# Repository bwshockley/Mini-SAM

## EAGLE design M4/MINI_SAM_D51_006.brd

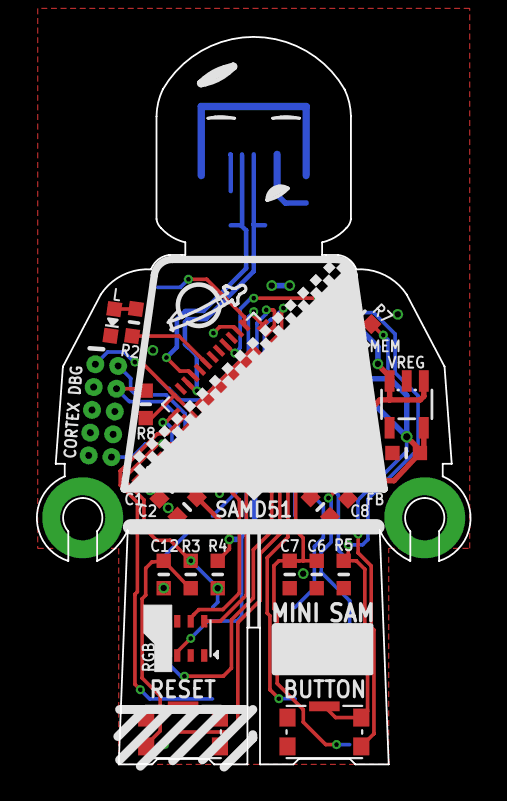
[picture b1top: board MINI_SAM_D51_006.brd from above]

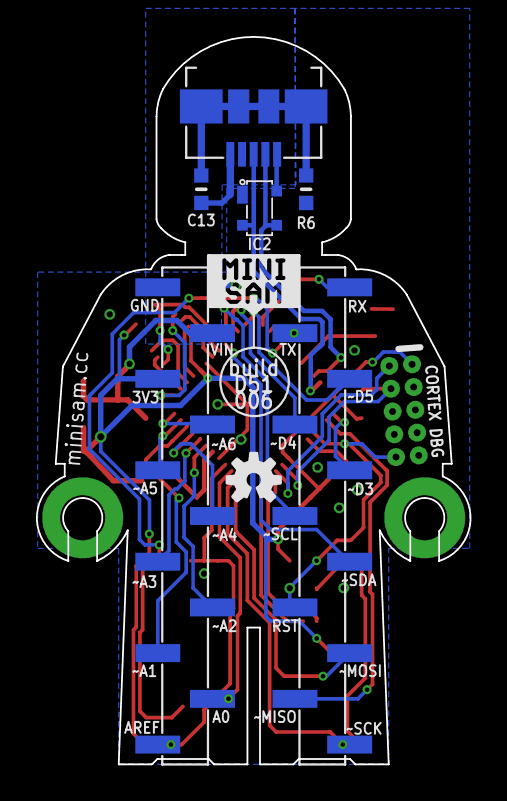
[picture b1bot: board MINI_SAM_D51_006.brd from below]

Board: 2 copper layers, 24.1 x 40.4 mm, 32 parts (7 on the bottom side), 41 nets.

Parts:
C1, C3, C7, C8, C12: 0.1µF; _0603MP
C2, C9, C10, C11: 10µF; _0603MP
C6: 4.7µF; _0603MP
C13: 4.7nF; _0603MP
FB: _0603MP
IC2: PRTR5V0U2X; SOT143B_REFLOW
IC4: ATSAMD51G_TQFN48; TQFN48_7MM
J1: MOLEX_47346-100147346; MOLEX_47346-1001
J2: CORTEX_DEBUG_PTH; 2X5-PTH-1.27MM
J3, J4: 1X11_SMT
L: CHIPLED_0603_NOOUTLINE
R2, R8: 1k; _0603MP
R3: 330Ohm; _0603MP
R4, R5: 10K; _0603MP
R6: 1M; _0603MP
R7: 100k; _0603MP
RGB: AP102-2020; APA102_2020
SW1, SW2: KMS233GLFG; KMS_SWITCH
U1: GD25x16; USON8
U$3: OSHW-LOGO-S
VREG: AP2112K-3.3V; SOT23-5

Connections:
!RESET: IC4.40, J2.10, J4.8, R3.1, R4.1
A0: IC4.3, J3.2
A1: IC4.10, J3.3
A2: IC4.7, J3.4
A3: IC4.8, J3.5
A4: IC4.9, J3.6
A5: IC4.11, J3.7
A6_D2: IC4.12, J3.8
AREF: C6.1, C7.1, IC4.4, J3.1
D3: IC4.37, J4.5
D4: IC4.23, J4.4
D5: IC4.24, J4.3
D9: IC4.28, R5.2, SW2.3, SW2.4
D13: IC4.31, R2.2
DOTSTAR_CLK: IC4.47, RGB.5
DOTSTAR_DATA: IC4.48, RGB.6
GND: C1.2, C2.2, C3.2, C6.2, C7.2, C8.2, C9.2, C10.1, C11.2, C12.1, C13.2, IC2.P1, IC4.5, IC4.18, IC4.35, IC4.42, IC4.THERMAL, J1.P5, J2.3, J2.5, J3.11, L.C, R5.1, R6.1, RGB.4, SW1.3, SW1.4, U1.4, VREG.2
MISO: IC4.38, J4.10
MOSI: IC4.1, J4.9
unnamed: C13.1, J1.PAD1, J1.PAD2, J1.PAD3, J1.PAD4, R6.2
unnamed: L.A, R2.1
unnamed: C12.2, R3.2, SW1.1
unnamed: C1.1, IC4.41
QSPI_CS: IC4.20, R7.2, U1.1
QSPI_DATA[0]: IC4.13, U1.5
QSPI_DATA[1]: IC4.14, U1.2
QSPI_DATA[2]: IC4.15, U1.3
QSPI_DATA[3]: IC4.16, U1.7
QSPI_SCK: IC4.19, U1.6
RX_D0: IC4.25, J4.1
SCK: IC4.2, J4.11
SCL: IC4.22, J4.6
SDA: IC4.21, J4.7
SWCLK: IC4.45, J2.4, R8.1
SWDIO: IC4.46, J2.2
TX_D1: IC4.26, J4.2
USBD+: IC2.P2, IC4.34, J1.P3
USBD-: IC2.P$3, IC4.33, J1.P2
VDD: C2.1, C3.1, C11.1, FB.1, IC4.17, IC4.36, IC4.44, J2.1, J3.9, R4.2, R7.1, R8.2, RGB.3, SW2.5, U1.8, VREG.5
VDDANA: C8.1, C9.1, FB.2, IC4.6
VIN: C10.2, IC2.P$4, J1.P1, J3.10, VREG.1, VREG.3

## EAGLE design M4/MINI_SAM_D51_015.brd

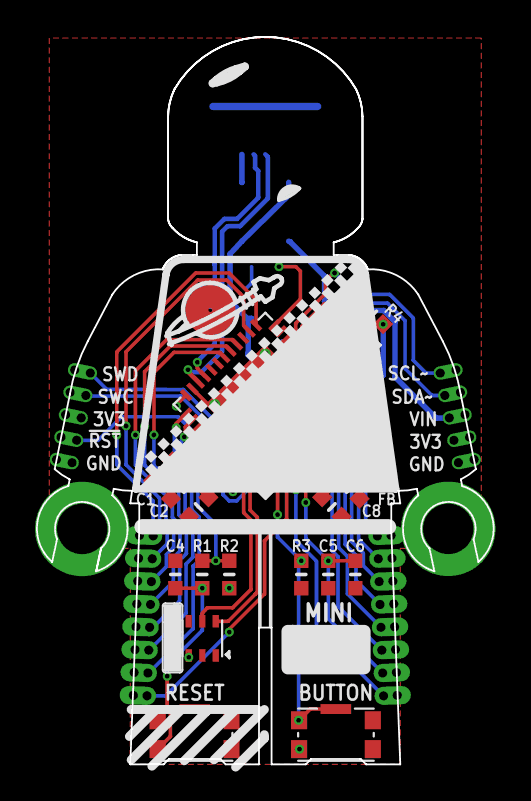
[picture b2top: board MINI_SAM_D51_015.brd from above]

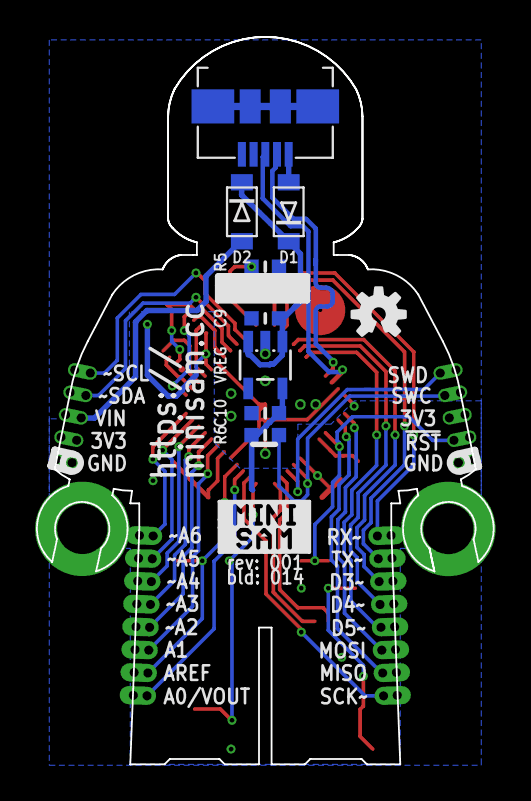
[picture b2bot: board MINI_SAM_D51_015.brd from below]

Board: 2 copper layers, 25.4 x 40.4 mm, 32 parts (10 on the bottom side), 42 nets.

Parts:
C1, C3, C4, C6, C8: 0.1µF; _0603MP
C2, C7, C9, C10: 10µF; _0603MP
C5: 4.7µF; _0603MP
D1, D2: MBR120; SOD-123FL
FB: _0603MP
J1: MOLEX_47346-100147346; MOLEX_47346-1001
J2, J4: 1X5_HEADER_1.27MMCAST; 1X5_HEADER_1.27MM_CASTELLATED
J3, J5: 1X8_HEADER_1.27MMCAST; 1X8_HEADER_1.27MM_CASTELLATED
LED: CHIPLED_0805_NOOUTLINE
R1: 1K; _0603MP
R2, R3: 10K; _0603MP
R4: 100k; _0603MP
R5, R6: 1k; _0603MP
RGB: AP102-2020; APA102_2020
SW1, SW2: KMS233GLFG; KMS_SWITCH
U1: ATSAMD51G_TQFN48; TQFN48_7MM
U2: GD25x16; USON8
U$3: OSHW-LOGO-S
VREG: AP2112K-3.3V; SOT23-5

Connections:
!RESET: J2.P4, R1.1, R2.1, U1.40
A0: J5.P1, U1.3
A1: J5.P3, U1.7
A2: J5.P4, U1.8
A3: J5.P5, U1.9
A4: J5.P6, U1.10
A5: J5.P7, U1.11
A6: J5.P8, U1.12
AREF: C5.1, C6.1, J5.P2, U1.4
BUTTON_D6: R3.2, SW2.2, SW2.3, U1.1
D3: J3.P3, U1.28
D4: J3.P4, U1.29
D5: J3.P5, U1.30
D14: R5.2, U1.24
DOTSTAR_CLK: RGB.5, U1.47
DOTSTAR_DATA: RGB.6, U1.48
GND: C1.2, C2.2, C3.2, C4.1, C5.2, C6.2, C7.2, C8.2, C9.1, C10.2, J1.P5, J1.PAD1, J1.PAD2, J1.PAD3, J1.PAD4, J2.P5, J4.P1, LED.C, R3.1, RGB.4, SW1.3, SW1.4, U1.5, U1.18, U1.35, U1.42, U1.THERMAL, U2.4, VREG.2
MISO: J3.P7, U1.38
MOSI: J3.P6, U1.37
unnamed: LED.A, R5.1
unnamed: C4.2, R1.2, SW1.1
unnamed: C1.1, U1.41
QSPI_CS: R4.2, U1.20, U2.1
QSPI_DATA[0]: U1.13, U2.5
QSPI_DATA[1]: U1.14, U2.2
QSPI_DATA[2]: U1.15, U2.3
QSPI_DATA[3]: U1.16, U2.7
QSPI_SCK: U1.19, U2.6
RX_D0: J3.P1, U1.25
SCK: J3.P8, U1.2
SCL: J4.P5, U1.22
SDA: J4.P4, U1.21
SWCLK: J2.P2, R6.1, U1.45
SWDIO: J2.P1, U1.46
TX_D1: J3.P2, U1.26
USBD+: J1.P3, U1.34
USBD-: J1.P2, U1.33
VDD: C2.1, C3.1, C10.1, FB.1, J2.P3, J4.P2, R2.2, R4.1, R6.2, RGB.3, SW2.1, U1.17, U1.36, U1.44, U2.8, VREG.5
VDDANA: C7.1, C8.1, FB.2, U1.6
VHI: C9.2, D1.C, D2.C, VREG.1, VREG.3
VIN: D2.A, J4.P3
VUSB: D1.A, J1.P1

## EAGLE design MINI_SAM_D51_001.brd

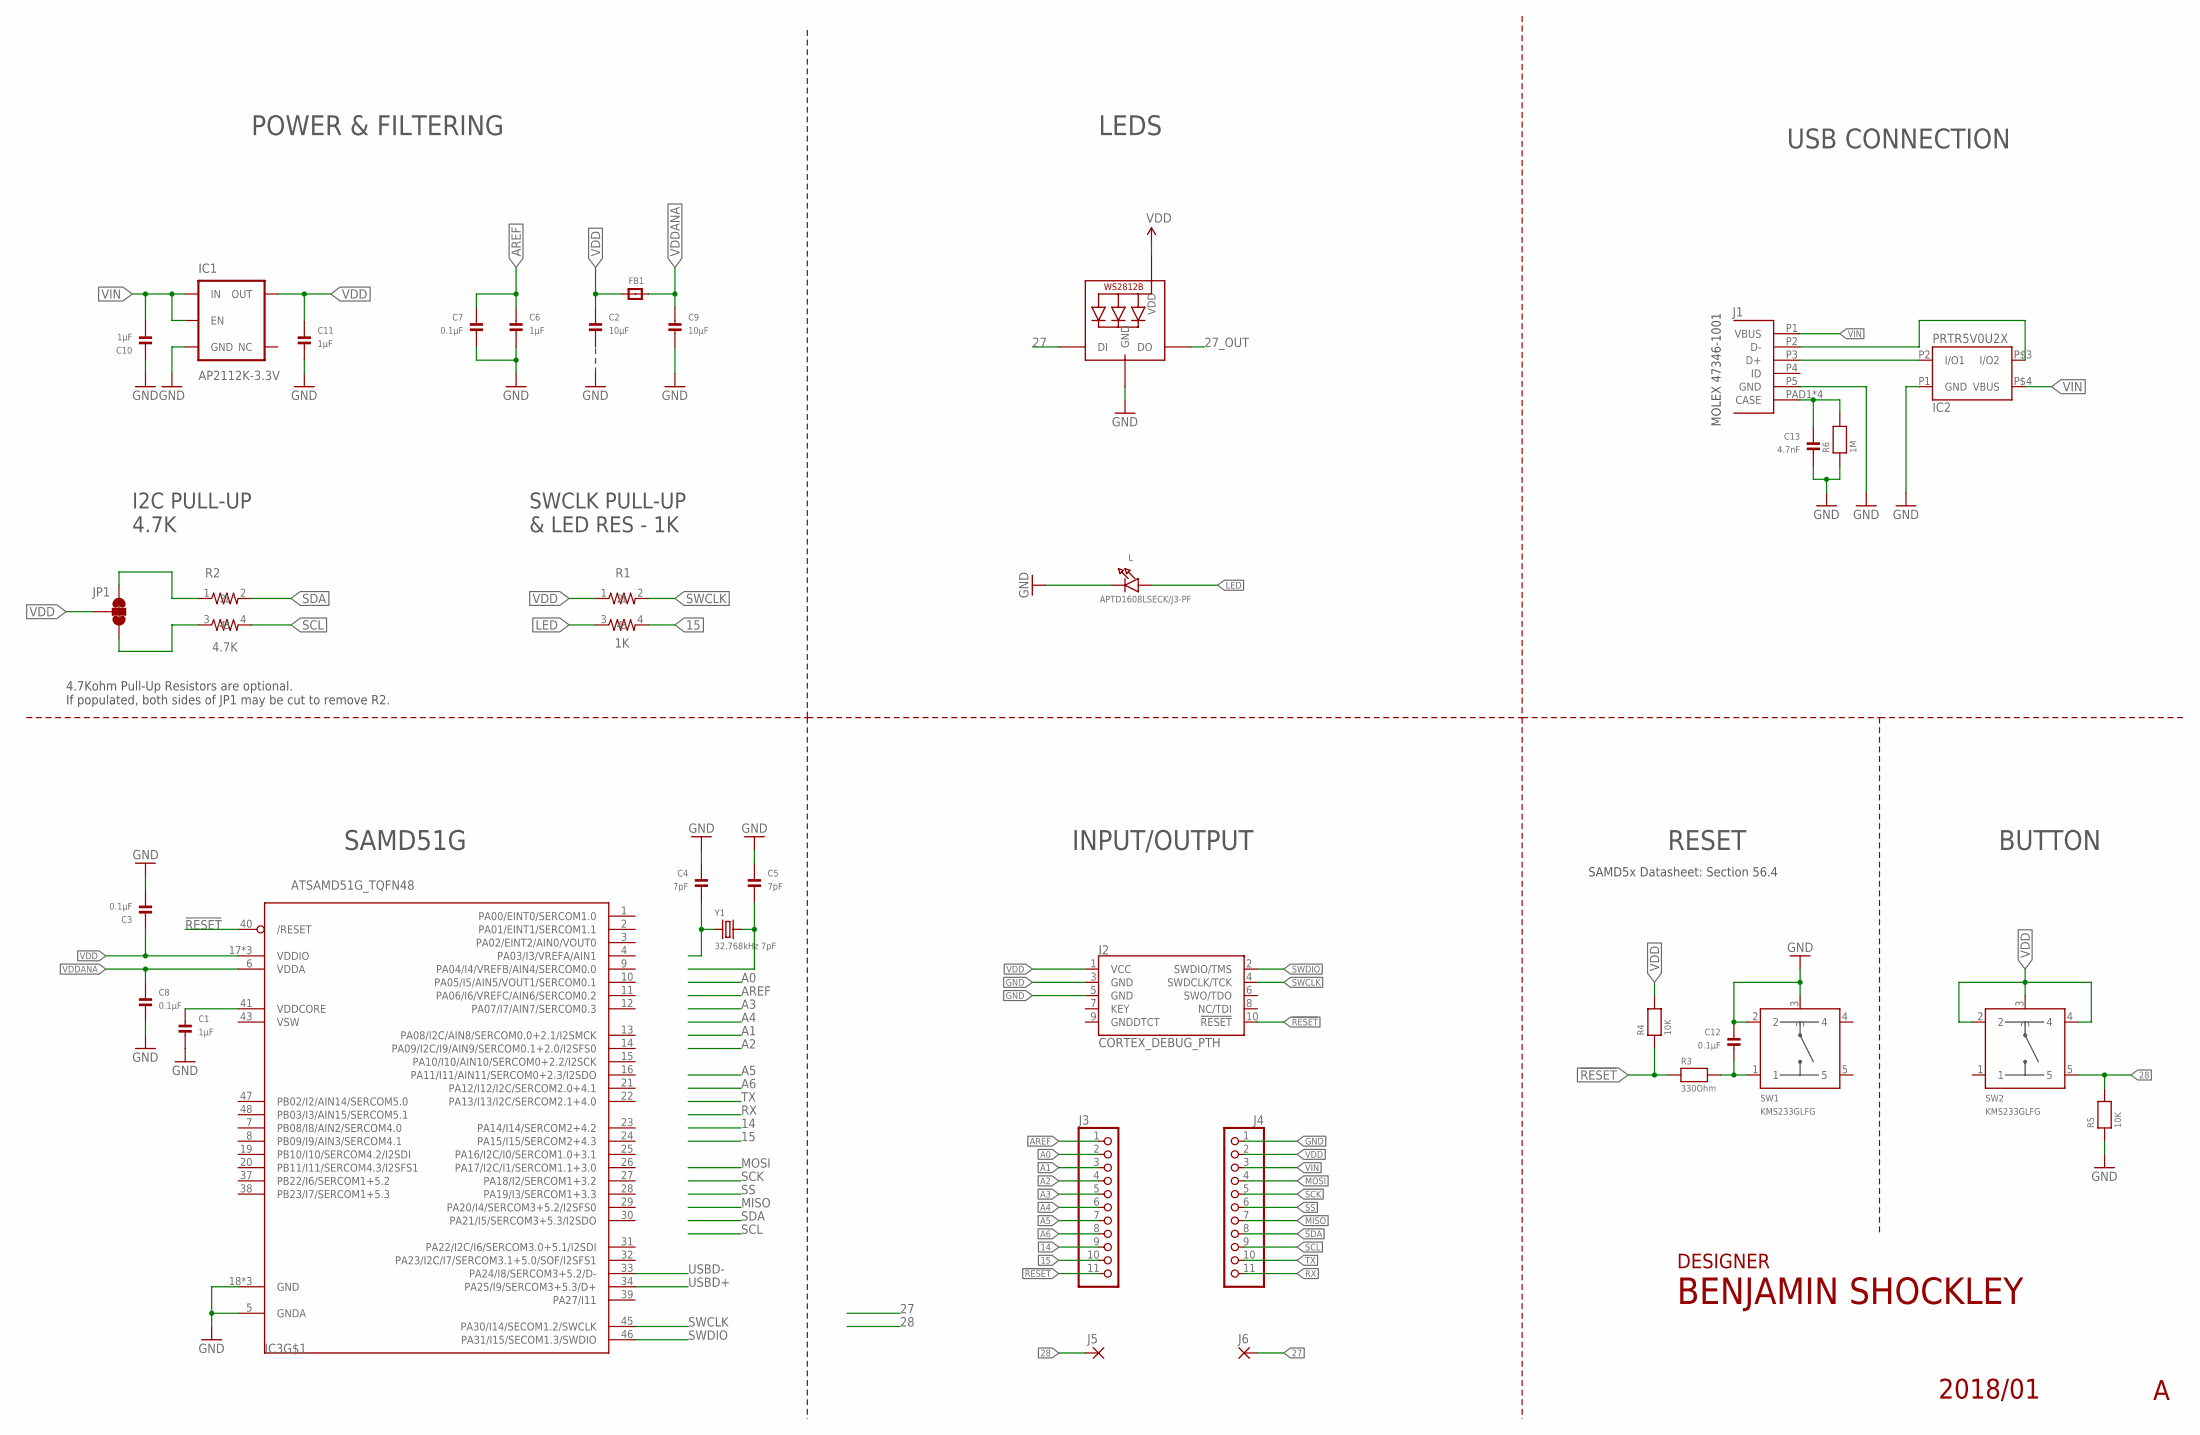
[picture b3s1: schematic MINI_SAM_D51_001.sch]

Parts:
C1, C6, C10, C11: 1µF; _0805MP
C2, C9: 10µF; _0805MP
C3, C7, C8, C12: 0.1µF; _0805MP
C4, C5: 7pF; _0805MP
C13: 4.7nF; _0805MP
FB1: FERRITE_0805MP; _0805MP
IC1: AP2112K-3.3V; SOT23-5
IC2: PRTR5V0U2X; SOT143B_REFLOW
IC3: ATSAMD51G_TQFN48; TQFN48_7MM
J1: MOLEX_47346-100147346; MOLEX_47346-1001
J2: CORTEX_DEBUG_PTH; 2X5-PTH-1.27MM
J3, J4: PINHD-1X111X11_SMT; 1X11_SMT
J5, J6: FR11_PAD2MMX1MM; SMD2MMX1MM
JP1: JUMPER-SMT_3_2-NC_TRACE_NO-SILK; SMT-JUMPER_3_2-NC_TRACE_NO-SILK
L: APTD1608LSECK/J3-PF; CHIPLED_0603_NOOUTLINE
R1: 1K; RESISTOR_ARRAY_0606
R2: 4.7K; RESISTOR_ARRAY_0606
R3: 330Ohm; _0805MP
R4, R5: 10K; _0805MP
R6: 1M; _0805MP
RGB: WS2812B3535; LED3535
SW1, SW2: KMS233GLFG; KMS_SWITCH
Y1: 32.768kHz 7pF; _0805MP

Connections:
14: J3.9
15: J3.10, R1.4
27: J6.P$1, RGB.1 (DI)
27_OUT: RGB.3 (DO)
28: J5.P$1, R5.2, SW2.5
!RESET: IC3.40 (/RESET), J2.10 (!RESET), J3.11, R3.1, R4.1
A0: J3.2
A1: J3.3
A2: J3.4
A3: J3.5
A4: J3.6
A5: J3.7
A6: J3.8
AREF: C6.1, C7.1, J3.1
GND: C1.2, C2.2, C3.2, C4.1, C5.1, C6.2, C7.2, C8.2, C9.2, C10.1, C11.2, C12.1, C13.2, IC1.2 (GND), IC2.P1 (GND), IC3.5 (GNDA), IC3.18 (GND), IC3.35 (GND), IC3.42 (GND), J1.P5 (GND), J2.3 (GND), J2.5 (GND), J4.1, L.C, R5.1, R6.1, RGB.4 (GND), SW1.2, SW1.3; also elsewhere on the board
LED: L.A, R1.3
MISO: J4.7
MOSI: J4.4
unnamed: C4.2, Y1.1
unnamed: C13.1, J1.PAD1 (CASE), J1.PAD2 (CASE), J1.PAD3 (CASE), J1.PAD4 (CASE), R6.2
unnamed: JP1.1, R2.1
unnamed: C12.2, R3.2, SW1.1
unnamed: C5.2, Y1.2
unnamed: JP1.3, R2.3
unnamed: C1.1, IC3.41 (VDDCORE)
RX: J4.11
SCK: J4.5
SCL: J4.9, R2.4
SDA: J4.8, R2.2
SS: J4.6
SWCLK: IC3.45 (PA30/I14/SECOM1.2/SWCLK), J2.4 (SWDCLK/TCK), R1.2
SWDIO: IC3.46 (PA31/I15/SECOM1.3/SWDIO), J2.2 (SWDIO/TMS)
TP: IC3.THERMAL (TP)
TX: J4.10
USBD+: IC2.P2 (I/O1), IC3.34 (PA25/I9/SERCOM3+5.3/D+), J1.P3 (D+)
USBD-: IC2.P$3 (I/O2), IC3.33 (PA24/I8/SERCOM3+5.2/D-), J1.P2 (D-)
VDD: C2.1, C3.1, C11.1, FB1.1, IC1.5 (OUT), IC3.17 (VDDIO), IC3.36 (VDDIO), IC3.44 (VDDIO), J2.1 (VCC), J4.2, JP1.2, R1.1, R4.2, RGB.2 (VDD), SW2.2, SW2.3, SW2.4
VDDANA: C8.1, C9.1, FB1.2, IC3.6 (VDDA)
VIN: C10.2, IC1.1 (IN), IC1.3 (EN), IC2.P$4 (VBUS), J1.P1 (VBUS), J4.3
VSW: IC3.43 (VSW); also elsewhere on the board

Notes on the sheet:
INPUT/OUTPUT
RESET
POWER & FILTERING
SAMD51G
LEDS
USB CONNECTION
I2C PULL-UP 4.7K
MOLEX 47346-1001
BUTTON
SWCLK PULL-UP & LED RES - 1K
DESIGNER
4.7Kohm Pull-Up Resistors are optional. If populated, both sides of JP1 may be cut to remove R2.
SAMD5x Datasheet: Section 56.4

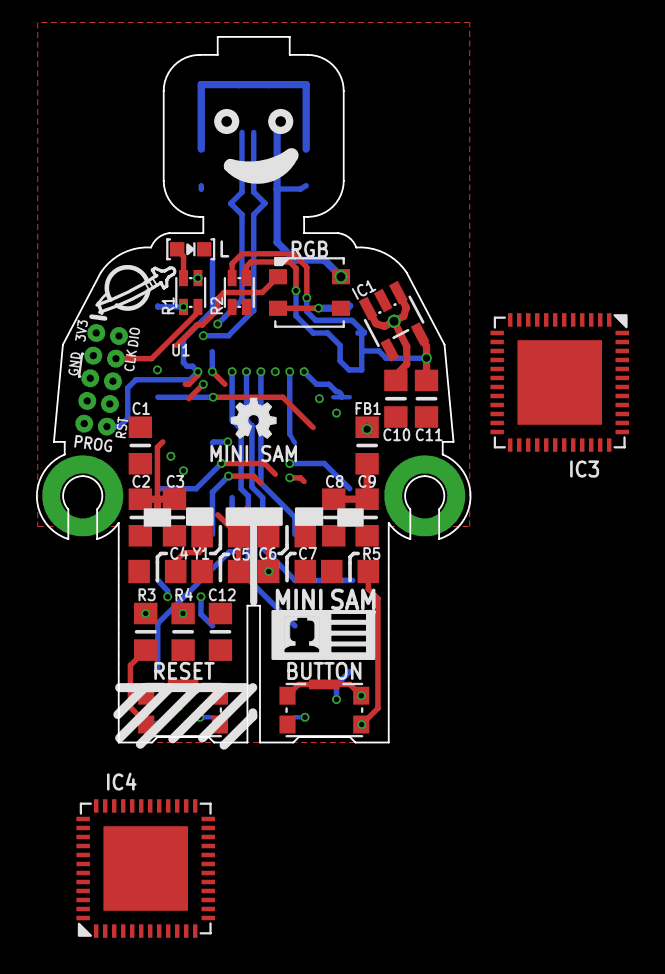
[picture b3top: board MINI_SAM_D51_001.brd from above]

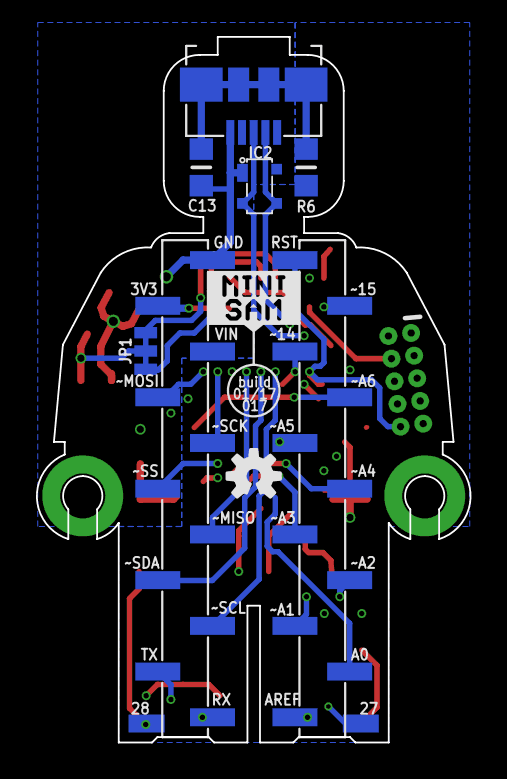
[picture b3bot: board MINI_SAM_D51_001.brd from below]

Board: 4 copper layers, 24.1 x 39.2 mm, 38 parts (10 on the bottom side), 25 nets.

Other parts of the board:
IC4: ATSAMD51G_TQFN48; TQFN48_7MM
U$1: OSHW-LOGO-MINI
U$3: OSHW-LOGO-S

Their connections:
GND: IC4.18, IC4.35, IC4.42, IC4.THERMAL; also elsewhere on the board
VDDIO: IC4.17, IC4.36, IC4.44
VSW: IC4.43; also elsewhere on the board

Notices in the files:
parts and their libraries:
microbuilder: This work is placed in the public domain, and may be freely used for commercial and non-commercial work with the following conditions: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
SparkFun-Aesthetics: Licensing: Creative Commons ShareAlike 4.0 International - https://creativecommons.org/licenses/by-sa/4.0
